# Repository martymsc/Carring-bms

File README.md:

# Carring-bms
Bms system for lithium based cells. Carring because it cares :D

The bms is based on an arduino leonardo board from Longan Labs (https://www.longan-labs.cc/1030008.html) and a battery monitor IC from Texas Instruments called BQ76PL455A.

Current revision:
 <ul>
  <li>  Battery cells voltage readout over serial</li>
  <li>  OV and UV protection with contactor control</li>
  <li>  Precharge circuit contorl</li>
  <li>  Isolation between contol MCU and battery  </li>
  <li>  Mcu supply is from the car, bms ic is powered by the battery </li>
 </ul> 
  
Problems:
<ul>
 <li>  Cell balancing is present but wasnt working in last revision</li>
 <li>  Same for the drain current measurment</li>
</ul>

Future goals:
<ul>
 <li>  Battery drain current measurment </li>
 <li>  Can bus logging implmentation</li>
 <li>  Switch to integrated MCU, either an STM or an RP </li>
 <li>  Fuel gauging</li>
 <li>  Charging control</li>
 <li>  Update the bms ic to a newer BQ79654</li>
 <li>  Add stackable funcionality</li>
</ul>

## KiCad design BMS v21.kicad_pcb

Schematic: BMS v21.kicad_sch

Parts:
C1, C18, C22, C23, C28: C0805C104K5RACTU; C0805; Mouser Part Number 80-C0805C104K5R
C2, C3, C4, C5, C6, C7, C8, C9, C10, C11, C12, C13, C14, C15, C16, C17, C25, C30: C2012X7S2A105K125AB; CAPC2012X145N; Mouser Part Number 810-C2012X7S2A105K
C19, C21, C24, C29: GRM31CR71H475KA12L; CAPC3216X180N; Mouser Part Number 81-GRM31CR71H475KA2L
C20: VJ0805D391KXCAJ; CAPC2012X145N; Mouser Part Number 77-VJ0805D391KXCAJ
C26: C0805C223K5RACTU; C0805; Mouser Part Number 80-C0805C223K5R
C27: C1210C185K3PACTU; C1210; Manufacturer_Part_Number C1210C185K3PACTU
D1, D2, D3, D4: 1N4148W; SODFL3816X120N; Mouser Part Number 637-1N4148W
IC1: BQ76PL455APFCR; QFP50P1400X1400X120-80N; Mouser Part Number 595-BQ76PL455APFCR
J1: 66201621122; Mouser Part Number 710-66201621122
J2: 66202021122; Mouser Part Number 710-66202021122
J3, J4: 43650-0420; 43650-04YY_18192063; Mouser Part Number 538-43650-0420
LED1, LED2, LED3, LED4, LED5, LED6, LED7, LED8, LED9, LED10, LED11, LED12, LED13, LED14: APHCM2012SYCK-F01; LEDC2012X50N; Mouser Part Number 604-APHCM2012SYCK
Q1, Q2, Q3, Q4, Q5, Q6, Q7, Q8, Q9, Q10, Q11, Q12, Q13, Q14: 2V7002KT1G; SOT96P237X111-3N; Mouser Part Number 863-2V7002KT1G
Q15: ZXTN4004KQTC; Mouser Part Number 621-ZXTN4004KQTC
R1, R2, R3, R4, R5, R6, R7, R8, R82, R86, R87, R88, R89, R90: RR1220P-104-D; RESC2013X65N; Mouser Part Number 754-RR1220P-104D
R9, R10, R11, R12, R13, R14, R15, R16, R17, R18, R19, R20, R21, R22: CRGCQ2512F33R; RESC6432X65N; Mouser Part Number 279-CRGCQ2512F33R
R23, R38, R40, R42, R43, R45, R47, R49, R51, R53, R55, R57, R59, R61, R63, R91: CRCW0805200RFKEA; RESC2012X50N; Mouser Part Number 71-CRCW0805-200-E3
R24, R25, R26, R27, R28, R29, R30, R31, R32, R33, R34, R35, R36, R37: RC0805FR-07100KL; RESC2012X60N; Mouser Part Number 603-RC0805FR-07100KL
R39, R41, R44, R46, R48, R50, R52, R54, R56, R58, R60, R62, R64, R80: ERJ-6GEYJ202V; RESC2013X65N; Mouser Part Number 667-ERJ-6GEYJ202V
R65, R66, R67, R68, R69, R70, R71, R72, R73, R74, R75, R76, R77, R78, R79: ERJ-8ENF1001V; ERJ8ENF1000V; Mouser Part Number 667-ERJ-8ENF1001V
R81: CRCW080551K0FKEA; RESC2012X50N; Mouser Part Number 71-CRCW080551K0FKEA
R83, R84, R85: ERJ-6ENF51R0V; ERJ6ENF1000V; Mouser Part Number 667-ERJ-6ENF51R0V
R92, R93: CRCW0805360RFKEA; RESC2012X50N; Mouser Part Number 71-CRCW0805360RFKEA
R94: ERJ-U6QJR39V; RESC2012X60N; Mouser Part Number 603-RC0805FR-07100KL
R95, R96: ERJ-8RQF1R0V; ERJ8_B_BW_R_LW_CW_D; Mouser Part Number 667-ERJ-8RQF1R0V
U1: CANBed v1.2e
Z1, Z2, Z3, Z4, Z5, Z6, Z7, Z8, Z9, Z10, Z11, Z12, Z13, Z14: MM3Z6V2T1G; SOD2512X110N; Mouser Part Number 863-MM3Z6V2T1G

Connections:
/+5V: U1.18 (5V)
/Arduino power on: J3.1, J4.4, U1.19 (VIN)
/Ballance1: IC1.28 (EQ1), R64.2 (R2)
/Ballance2: IC1.26 (EQ2), R62.2 (R2)
/Ballance3: IC1.24 (EQ3), R60.2 (R2)
/Ballance4: IC1.22 (EQ4), R58.2 (R2)
/Ballance5: IC1.20 (EQ5), R56.2 (R2)
/Ballance6: IC1.18 (EQ6), R54.2 (R2)
/Ballance7: IC1.16 (EQ7), R52.2 (R2)
/Ballance8: IC1.14 (EQ8), R50.2 (R2)
/Ballance9: IC1.12 (EQ9), R48.2 (R2)
/Ballance10: IC1.10 (EQ10), R46.2 (R2)
/Ballance11: IC1.8 (EQ11), R44.2 (R2)
/Ballance12: IC1.6 (EQ12), R80.1 (R1)
/Ballance13: IC1.4 (EQ13), R41.2 (R2)
/Ballance14: IC1.2 (EQ14), R39.2 (R2)
/CAN H: J3.4, U1.21 (CANH)
/CAN L: J3.3, U1.22 (CANL)
/Current_sense_OUT: U1.12 (A0)
/FALUT_N: R83.2, U1.2 (D4)
/NPN_BASE: IC1.71 (NPNB), Q15.1 (B)
/OUT: C20.1, IC1.68 (OUT2), IC1.73 (OUT1)
/Precharge IN: J4.2, U1.15 (D11)
/Precharge OUT: J4.1, U1.13 (D10)
/RX: R84.2, R88.1 (R1), U1.3 (D1/TX)
/TX: R85.2, R89.1 (R1), U1.1 (D0/RX)
/TempIN1: IC1.66 (AUX0), J1.9, R1.1 (R1)
/TempIN2: IC1.65 (AUX1), J1.10, R2.1 (R1)
/TempIN3: IC1.64 (AUX2), J1.11, R3.1 (R1)
/TempIN4: IC1.63 (AUX3), J1.12, R4.1 (R1)
/TempIN5: IC1.62 (AUX4), J1.13, R5.1 (R1)
/TempIN6: IC1.61 (AUX5), J1.14, R6.1 (R1)
/TempIN7: IC1.60 (AUX6), J1.15, R7.1 (R1)
/TempIN8: IC1.59 (AUX7), J1.16, R8.1 (R1)
/V5VAO: C24.1, IC1.58 (V5VAO), R87.1 (R1)
/VDIG: C18.2, C21.2, IC1.34 (VDIG), R95.1
/VIO: C23.2, C25.2, IC1.41 (VIO), R88.2 (R2), R89.2 (R2), R96.1
/VP1: IC1.70 (VP), Q15.3 (E), R1.2 (R2), R2.2 (R2), R3.2 (R2), R4.2 (R2), R5.2 (R2), R6.2 (R2), R7.2 (R2), R8.2 (R2), R94.2, R95.2, R96.2
/Vsense1(4.2V): J2.18, Q13.3 (D), R22.2, R36.1, R78.1
/Vsense1_OUT: C15.2, IC1.27 (VSENSE1), LED14.2 (A), R78.2, Z13.2 (A), Z14.1 (K); also elsewhere on the board
/Vsense2(8.4V): J2.8, Q12.3 (D), R21.2, R35.1, R77.1
/Vsense2_OUT: C14.2, IC1.25 (VSENSE2), LED13.2 (A), R77.2, Z12.2 (A), Z13.1 (K); also elsewhere on the board
/Vsense3(12.6V): J2.17, Q11.3 (D), R20.2, R34.1, R76.1
/Vsense3_OUT: C13.2, IC1.23 (VSENSE3), LED12.2 (A), R76.2, Z11.2 (A), Z12.1 (K); also elsewhere on the board
/Vsense4(16.8V): J2.7, Q10.3 (D), R19.2, R33.1, R75.1
/Vsense4_OUT: C12.2, IC1.21 (VSENSE4), LED11.2 (A), R75.2, Z10.2 (A), Z11.1 (K); also elsewhere on the board
/Vsense5(21V): J2.16, Q9.3 (D), R18.2, R32.1, R74.1
/Vsense5_OUT: C11.2, IC1.19 (VSENSE5), LED10.2 (A), R74.2, Z9.2 (A), Z10.1 (K); also elsewhere on the board
/Vsense6(25.2V): J2.6, Q8.3 (D), R17.2, R31.1, R73.1
/Vsense6_OUT: C10.2, IC1.17 (VSENSE6), LED9.2 (A), R73.2, Z8.2 (A), Z9.1 (K); also elsewhere on the board
/Vsense7(29.4V): J2.15, Q7.3 (D), R16.2, R30.1, R72.1
/Vsense7_OUT: C9.2, IC1.15 (VSENSE7), LED8.2 (A), R72.2, Z7.2 (A), Z8.1 (K); also elsewhere on the board
/Vsense8(33.6V): J2.5, Q6.3 (D), R15.2, R29.1, R71.1
/Vsense8_OUT: C8.2, IC1.13 (VSENSE8), LED7.2 (A), R71.2, Z6.2 (A), Z7.1 (K); also elsewhere on the board
/Vsense9(37.8V): J2.14, Q5.3 (D), R14.2, R28.1, R70.1
/Vsense9_OUT: C7.2, IC1.11 (VSENSE9), LED6.2 (A), R70.2, Z5.2 (A), Z6.1 (K); also elsewhere on the board
/Vsense10(42V): J2.4, Q4.3 (D), R13.2, R27.1, R69.1
/Vsense10_OUT: C6.2, IC1.9 (VSENSE10), LED5.2 (A), R69.2, Z4.2 (A), Z5.1 (K); also elsewhere on the board
/Vsense11(46.2V): J2.13, Q3.3 (D), R12.2, R26.1, R68.1
/Vsense11_OUT: C5.2, IC1.7 (VSENSE11), LED4.2 (A), R68.2, Z3.2 (A), Z4.1 (K); also elsewhere on the board
/Vsense12(50.4V): J2.3, Q2.3 (D), R11.2, R25.1, R67.1
/Vsense12_OUT: C4.2, IC1.5 (VSENSE12), LED3.2 (A), R67.2, Z2.2 (A), Z3.1 (K); also elsewhere on the board
/Vsense13(54.6V): J2.12, Q1.3 (D), R10.2, R24.1, R66.1
/Vsense13_OUT: C3.2, IC1.3 (VSENSE13), LED2.2 (A), R66.2, Z1.2 (A), Z2.1 (K); also elsewhere on the board
/Vsense14(58.8V): J2.1, J2.2, J2.11, R9.2, R23.1, R65.1, R92.2
/WAKEUP: R91.2, U1.4 (D5)
unnamed: C29.2, R94.1
unnamed: C26.2, IC1.33 (CHM)
unnamed: C26.1, IC1.32 (CHP)
unnamed: IC1.52 (COMML+), R87.2 (R2)
unnamed: IC1.53 (COMML-), R86.2 (R2)
unnamed: IC1.40 (FAULT__N), R81.1, R83.1
unnamed: IC1.42 (GPIO5), IC1.43 (GPIO4), IC1.44 (GPIO3), IC1.45 (GPIO2), IC1.46 (GPIO1), IC1.47 (GPIO0), R82.1 (R1)
unnamed: IC1.39 (RX), R84.1
unnamed: IC1.38 (TX), R85.1
unnamed: C19.2, C22.2, IC1.31 (VM)
unnamed: C27.2, C28.2, IC1.67 (VR_EF)
unnamed: IC1.49 (WAKEUP), R90.2 (R2), R91.1
unnamed 78: LED1.1 (K), R38.2; also elsewhere on the board
unnamed 79: LED2.1 (K), R40.2; also elsewhere on the board
unnamed 80: LED3.1 (K), R42.2; also elsewhere on the board
unnamed 81: LED4.1 (K), R43.2; also elsewhere on the board
unnamed 82: LED5.1 (K), R45.2; also elsewhere on the board
unnamed 83: LED6.1 (K), R47.2; also elsewhere on the board
unnamed 84: LED7.1 (K), R49.2; also elsewhere on the board
unnamed 85: LED8.1 (K), R51.2; also elsewhere on the board
unnamed 86: LED9.1 (K), R53.2; also elsewhere on the board
unnamed 87: LED10.1 (K), R55.2; also elsewhere on the board
unnamed 88: LED11.1 (K), R57.2; also elsewhere on the board
unnamed 89: LED12.1 (K), R59.2; also elsewhere on the board
unnamed 90: LED13.1 (K), R61.2; also elsewhere on the board
unnamed 91: LED14.1 (K), R63.2; also elsewhere on the board
unnamed: Q1.1 (G), R24.2, R39.1 (R1)
unnamed: Q1.2 (S), R9.1, R38.1
unnamed: Q2.1 (G), R25.2, R41.1 (R1)
unnamed: Q2.2 (S), R10.1, R40.1
unnamed: Q3.1 (G), R26.2, R80.2 (R2)
unnamed: Q3.2 (S), R11.1, R42.1
unnamed: Q4.1 (G), R27.2, R44.1 (R1)
unnamed: Q4.2 (S), R12.1, R43.1
unnamed: Q5.1 (G), R28.2, R46.1 (R1)
unnamed: Q5.2 (S), R13.1, R45.1
unnamed: Q6.1 (G), R29.2, R48.1 (R1)
unnamed: Q6.2 (S), R14.1, R47.1
unnamed: Q7.1 (G), R30.2, R50.1 (R1)
unnamed: Q7.2 (S), R15.1, R49.1
unnamed: Q8.1 (G), R31.2, R52.1 (R1)
unnamed: Q8.2 (S), R16.1, R51.1
unnamed: Q9.1 (G), R32.2, R54.1 (R1)
unnamed: Q9.2 (S), R17.1, R53.1
unnamed: Q10.1 (G), R33.2, R56.1 (R1)
unnamed: Q10.2 (S), R18.1, R55.1
unnamed: Q11.1 (G), R34.2, R58.1 (R1)
unnamed: Q11.2 (S), R19.1, R57.1
unnamed: Q12.1 (G), R35.2, R60.1 (R1)
unnamed: Q12.2 (S), R20.1, R59.1
unnamed: Q13.1 (G), R36.2, R62.1 (R1)
unnamed: Q13.2 (S), R21.1, R61.1
unnamed: Q14.1 (G), R37.2, R64.1 (R1)
unnamed: Q14.2 (S), R22.1, R63.1
unnamed: C30.1, Q15.2 (C), R93.1
unnamed: R92.1, R93.2

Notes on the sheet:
Konektor pro tep. sondy
Konnektor pro balancování a nabíjení

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
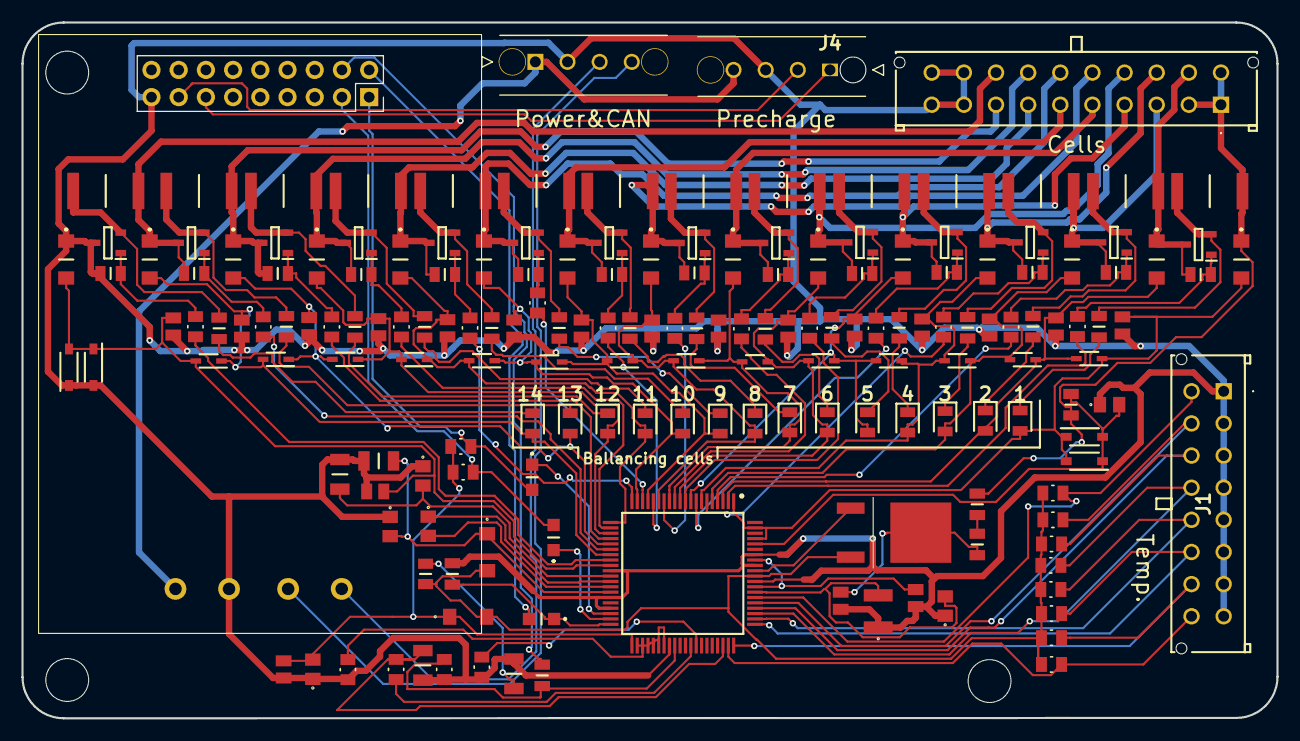
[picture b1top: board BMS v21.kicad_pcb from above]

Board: 2 copper layers, 117.2 x 65.0 mm, 179 parts (0 on the bottom side), 124 nets.

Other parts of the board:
1, 2, 3, 4, 5, 6, 7, 8, 9, 10, 11, 12, 13, 14: APHCM2012SYCK-F01; LEDC2012X50N

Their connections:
/Vsense1_OUT: 14.2 (A); also elsewhere on the board
/Vsense2_OUT: 13.2 (A); also elsewhere on the board
/Vsense3_OUT: 12.2 (A); also elsewhere on the board
/Vsense4_OUT: 11.2 (A); also elsewhere on the board
/Vsense5_OUT: 10.2 (A); also elsewhere on the board
/Vsense6_OUT: 9.2 (A); also elsewhere on the board
/Vsense7_OUT: 8.2 (A); also elsewhere on the board
/Vsense8_OUT: 7.2 (A); also elsewhere on the board
/Vsense9_OUT: 6.2 (A); also elsewhere on the board
/Vsense10_OUT: 5.2 (A); also elsewhere on the board
/Vsense11_OUT: 4.2 (A); also elsewhere on the board
/Vsense12_OUT: 3.2 (A); also elsewhere on the board
/Vsense13_OUT: 2.2 (A); also elsewhere on the board
unnamed 78: 1.1 (K); also elsewhere on the board
unnamed 79: 2.1 (K); also elsewhere on the board
unnamed 80: 3.1 (K); also elsewhere on the board
unnamed 81: 4.1 (K); also elsewhere on the board
unnamed 82: 5.1 (K); also elsewhere on the board
unnamed 83: 6.1 (K); also elsewhere on the board
unnamed 84: 7.1 (K); also elsewhere on the board
unnamed 85: 8.1 (K); also elsewhere on the board
unnamed 86: 9.1 (K); also elsewhere on the board
unnamed 87: 10.1 (K); also elsewhere on the board
unnamed 88: 11.1 (K); also elsewhere on the board
unnamed 89: 12.1 (K); also elsewhere on the board
unnamed 90: 13.1 (K); also elsewhere on the board
unnamed 91: 14.1 (K); also elsewhere on the board

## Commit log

2024-09-09 Inital commit
